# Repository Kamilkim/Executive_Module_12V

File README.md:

# Executive_Module_12V
Executive module to control devices on voltage 12V

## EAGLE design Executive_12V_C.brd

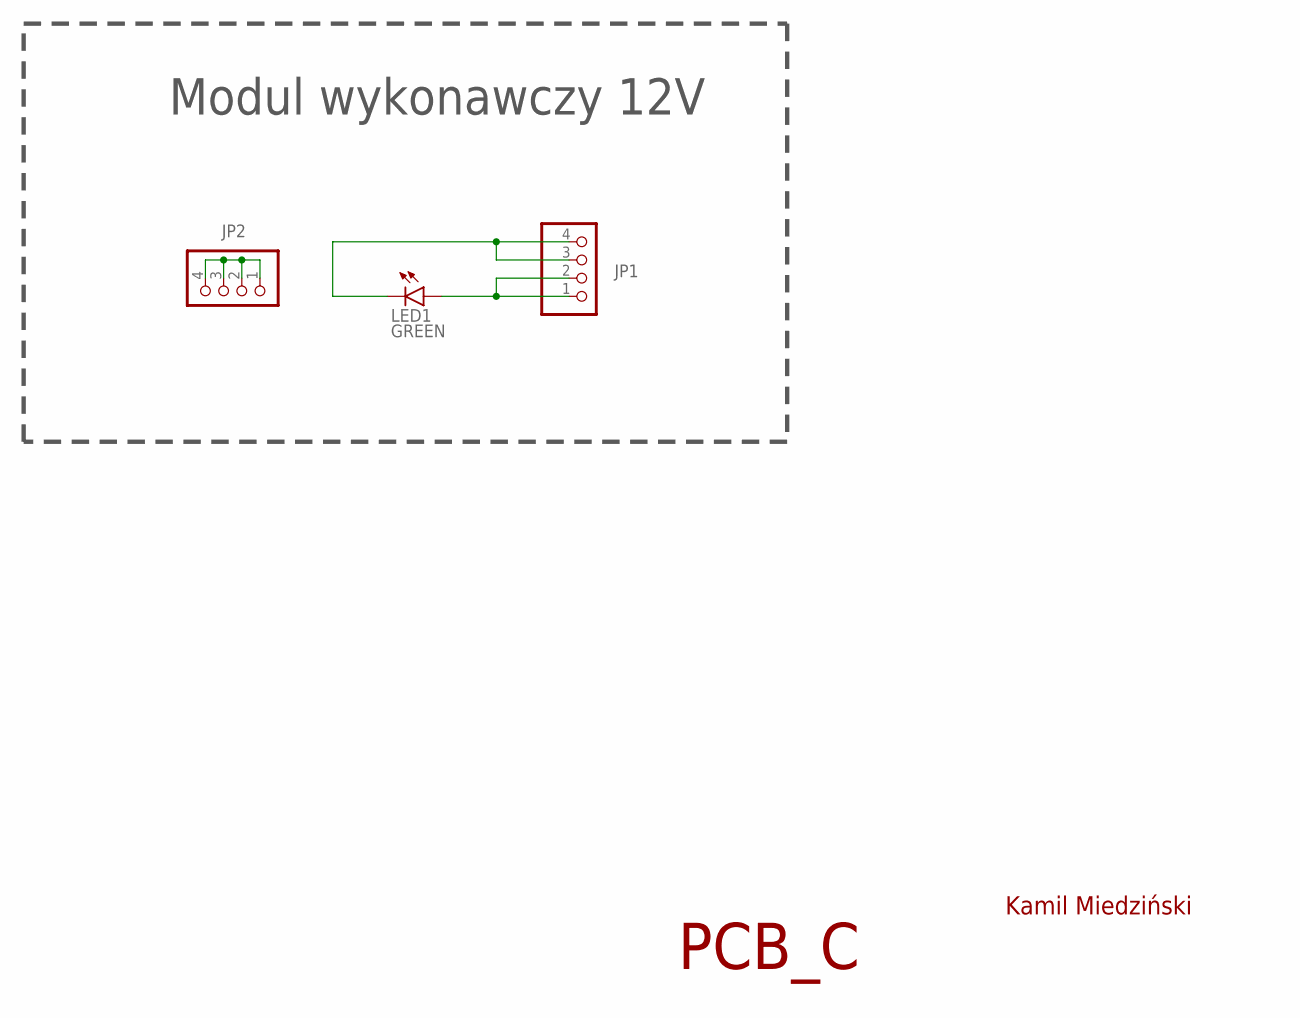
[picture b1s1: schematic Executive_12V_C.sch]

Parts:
JP1, JP2: PINHD-1X41X04H; 1X04H
LED1: GREEN; LED5MM_GREEN

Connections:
unnamed: JP1.1, JP1.2, LED1.A
unnamed: JP1.3, JP1.4, LED1.K (C)
unnamed: JP2.1, JP2.2, JP2.3, JP2.4

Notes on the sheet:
Kamil Miedziński
Modul wykonawczy 12V
PCB_C

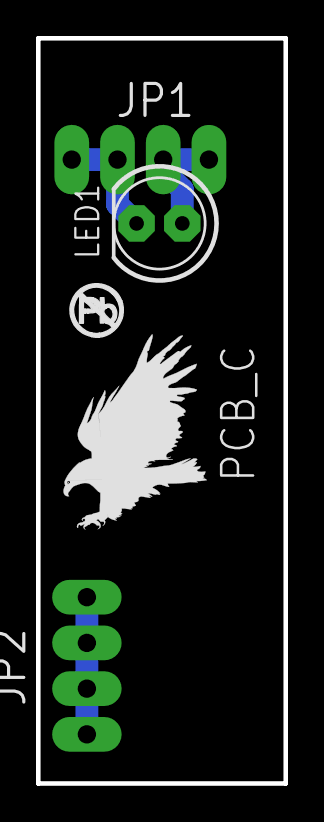
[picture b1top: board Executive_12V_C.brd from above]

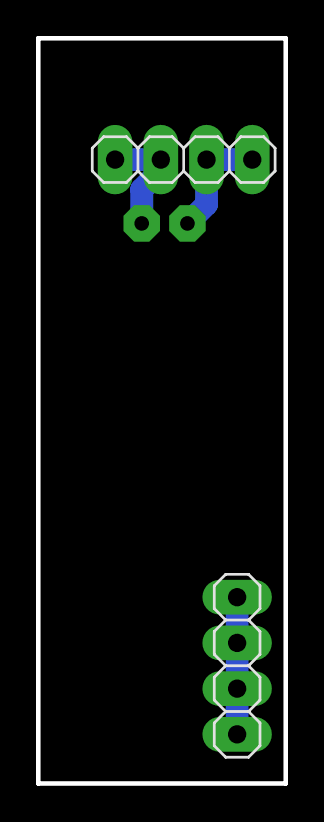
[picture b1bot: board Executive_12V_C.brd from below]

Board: 2 copper layers, 13.7 x 41.4 mm, 5 parts (2 on the bottom side), 3 nets.

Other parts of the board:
U$1: EAGLE-PLC-8MM
U$2: NO_PB_LOGO_0.120

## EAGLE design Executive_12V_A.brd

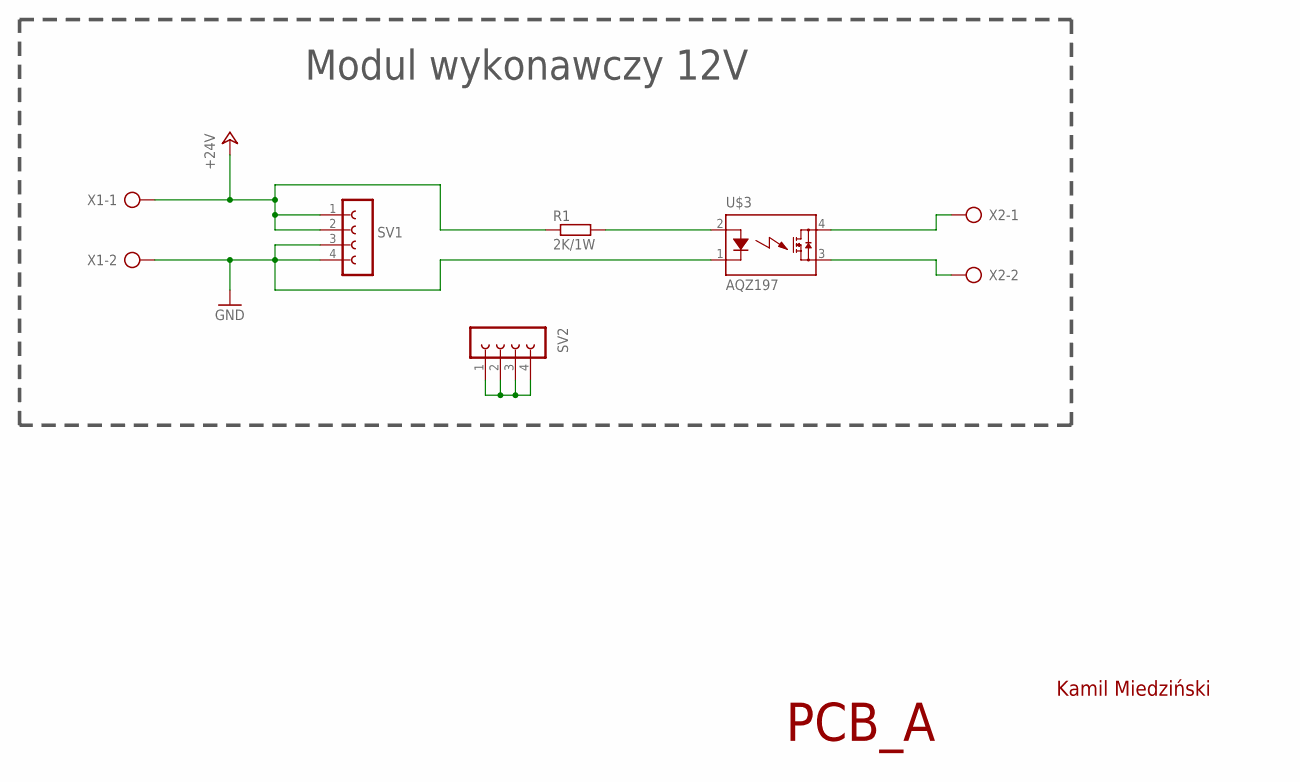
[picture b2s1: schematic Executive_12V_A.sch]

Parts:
R1: 2K/1W; 0411/15
SV1, SV2: FE04-1
U$3: AQZ197; AQZ-SIL04
X1, X2: GMKDSP_3/2

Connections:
+24V: R1.1, SV1.1 (2), SV1.2 (3), X1.1
GND: SV1.3 (4), SV1.4 (5), U$3.1 (K), X1.2
unnamed: U$3.4 (DS1), X2.1
unnamed: R1.2, U$3.2 (A)
unnamed: U$3.3 (DS2), X2.2
unnamed: SV2.1 (2), SV2.2 (3), SV2.3 (4), SV2.4 (5)

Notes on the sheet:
Kamil Miedziński
Modul wykonawczy 12V
PCB_A

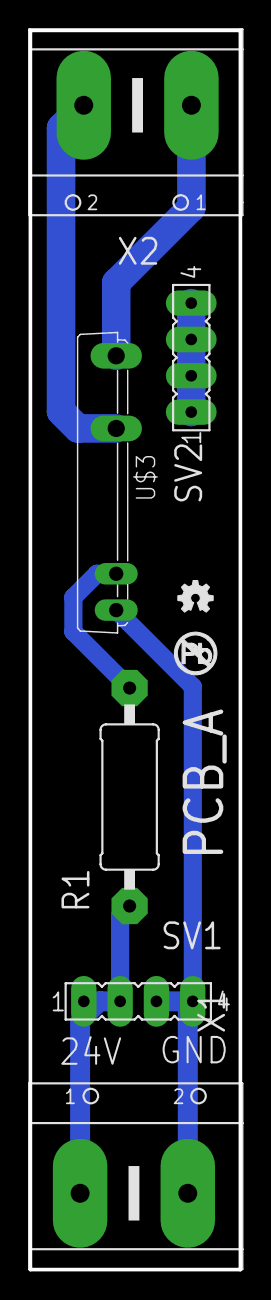
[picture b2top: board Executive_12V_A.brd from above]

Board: 2 copper layers, 14.7 x 86.6 mm, 8 parts (0 on the bottom side), 6 nets.

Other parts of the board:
U$1: NO_PB_LOGO_0.120
U$2: OSHW-LOGO-MINI

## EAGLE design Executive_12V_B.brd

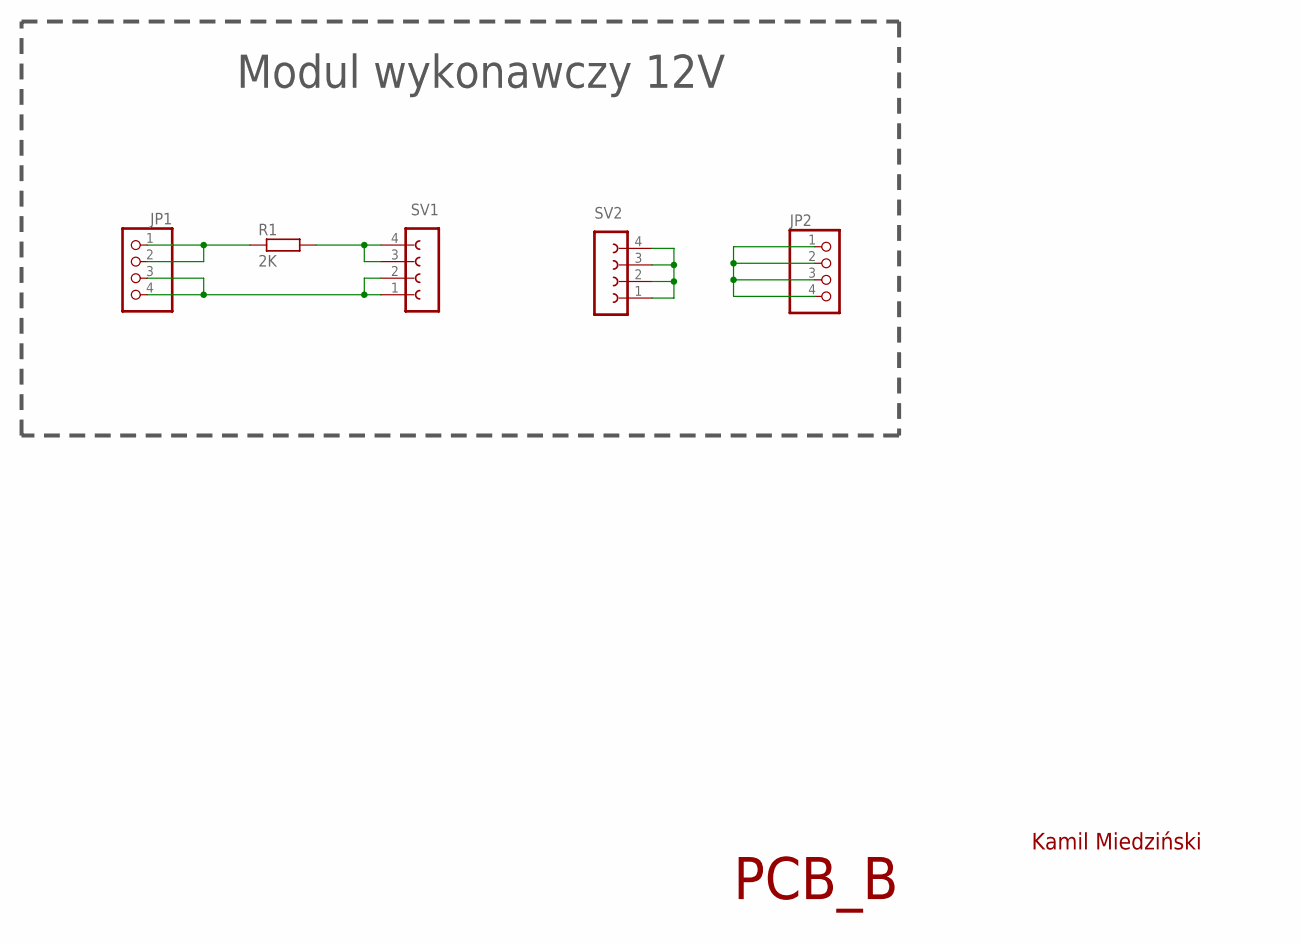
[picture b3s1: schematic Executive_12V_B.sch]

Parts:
JP1, JP2: PINHD-1X41X04H; 1X04H
R1: 2K; 0207/10
SV1, SV2: FE04-1

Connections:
unnamed: JP1.3, JP1.4, SV1.1 (2), SV1.2 (3)
unnamed: JP1.1, JP1.2, R1.1
unnamed: R1.2, SV1.3 (4), SV1.4 (5)
unnamed: SV2.1 (2), SV2.2 (3), SV2.3 (4), SV2.4 (5)
unnamed: JP2.1, JP2.2, JP2.3, JP2.4

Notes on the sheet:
Kamil Miedziński
Modul wykonawczy 12V
PCB_B

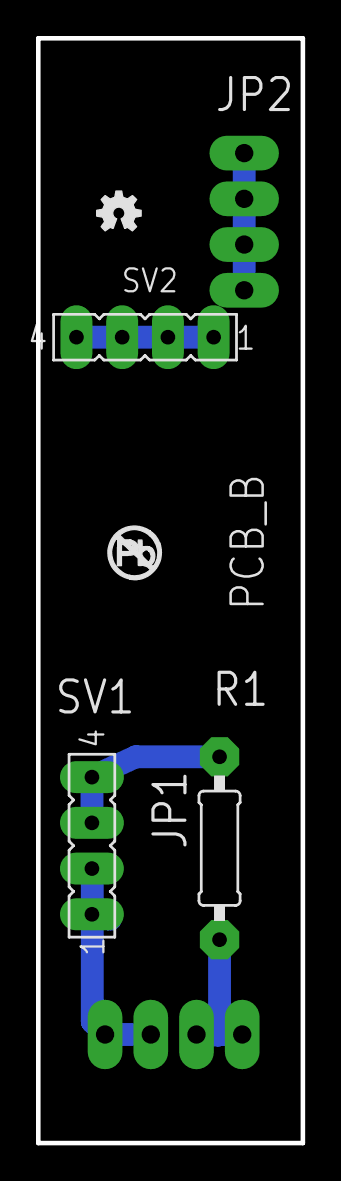
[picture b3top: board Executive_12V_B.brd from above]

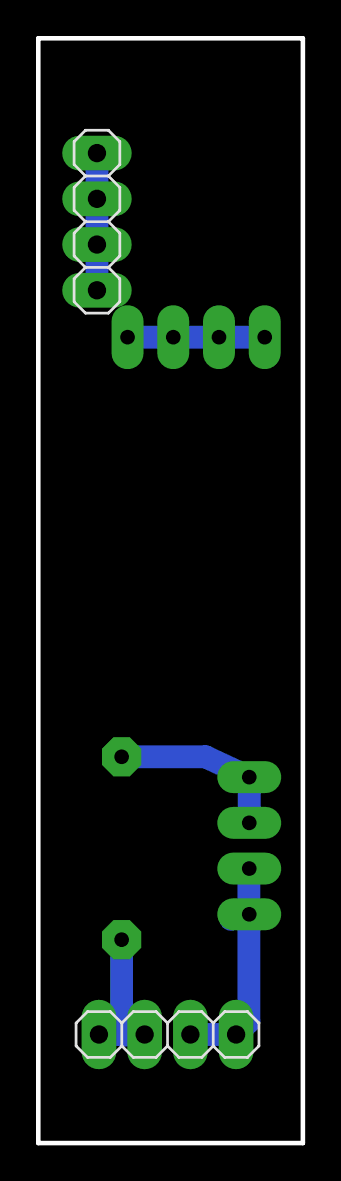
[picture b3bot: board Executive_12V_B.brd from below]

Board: 2 copper layers, 14.7 x 61.4 mm, 7 parts (2 on the bottom side), 5 nets.

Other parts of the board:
U$1: OSHW-LOGO-MINI
U$2: NO_PB_LOGO_0.120

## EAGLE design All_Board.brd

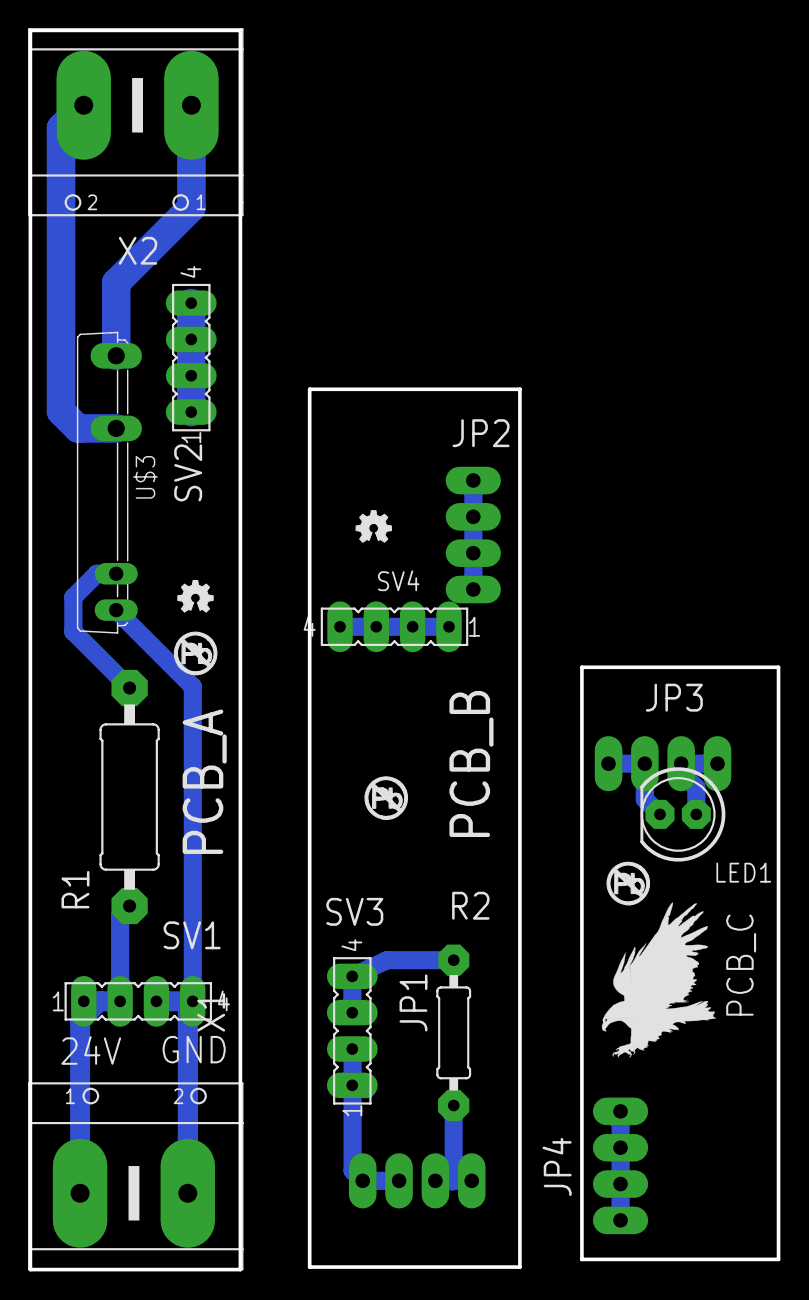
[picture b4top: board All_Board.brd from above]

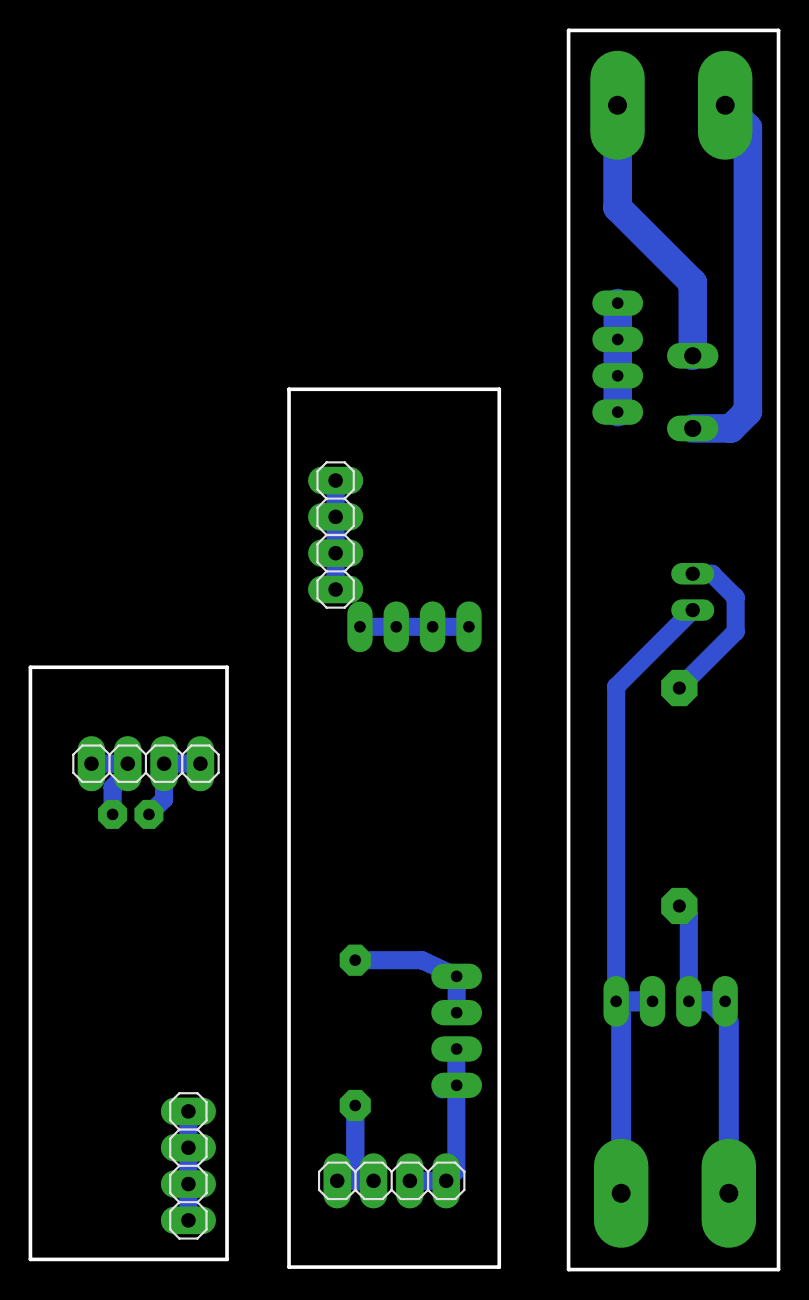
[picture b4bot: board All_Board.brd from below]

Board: 2 copper layers, 52.3 x 86.6 mm, 20 parts (4 on the bottom side), 14 nets.

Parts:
JP1, JP2, JP3, JP4: 1X04H
LED1: GREEN; LED5MM_GREEN
R1: 2K/1W; 0411/15
R2: 2K; 0207/10
SV1, SV2, SV3, SV4: FE04-1
U$1, U$5, U$7: NO_PB_LOGO_0.120
U$2, U$4: OSHW-LOGO-MINI
U$3: AQZ197; AQZ-SIL04
U$6: EAGLE-PLC-8MM
X1, X2: GMKDSP_3/2

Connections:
+24V: R1.1, SV1.1, SV1.2, X1.1
GND: SV1.3, SV1.4, U$3.1, X1.2
unnamed: U$3.4, X2.1
unnamed: R1.2, U$3.2
unnamed: U$3.3, X2.2
unnamed: SV2.1, SV2.2, SV2.3, SV2.4
unnamed: R2.2, SV3.3, SV3.4
unnamed: JP1.1, JP1.2, R2.1
unnamed: JP2.1, JP2.2, JP2.3, JP2.4
unnamed: JP1.3, JP1.4, SV3.1, SV3.2
unnamed: SV4.1, SV4.2, SV4.3, SV4.4
unnamed: JP3.1, JP3.2, LED1.A
unnamed: JP3.3, JP3.4, LED1.K
unnamed: JP4.1, JP4.2, JP4.3, JP4.4

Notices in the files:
parts and their libraries:
SparkFun-Aesthetics: Licensing: Creative Commons ShareAlike 4.0 International - https://creativecommons.org/licenses/by-sa/4.0
